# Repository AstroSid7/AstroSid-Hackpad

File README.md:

# AstroSid-Hackpad
A custom 6-key mechanical macropad featuring a rotary encoder for media and volume control. Designed with a 2-layer PCB, a 3D-printed case, and powered by the Seeed XIAO RP2040 using KMK (CircuitPython) firmware.

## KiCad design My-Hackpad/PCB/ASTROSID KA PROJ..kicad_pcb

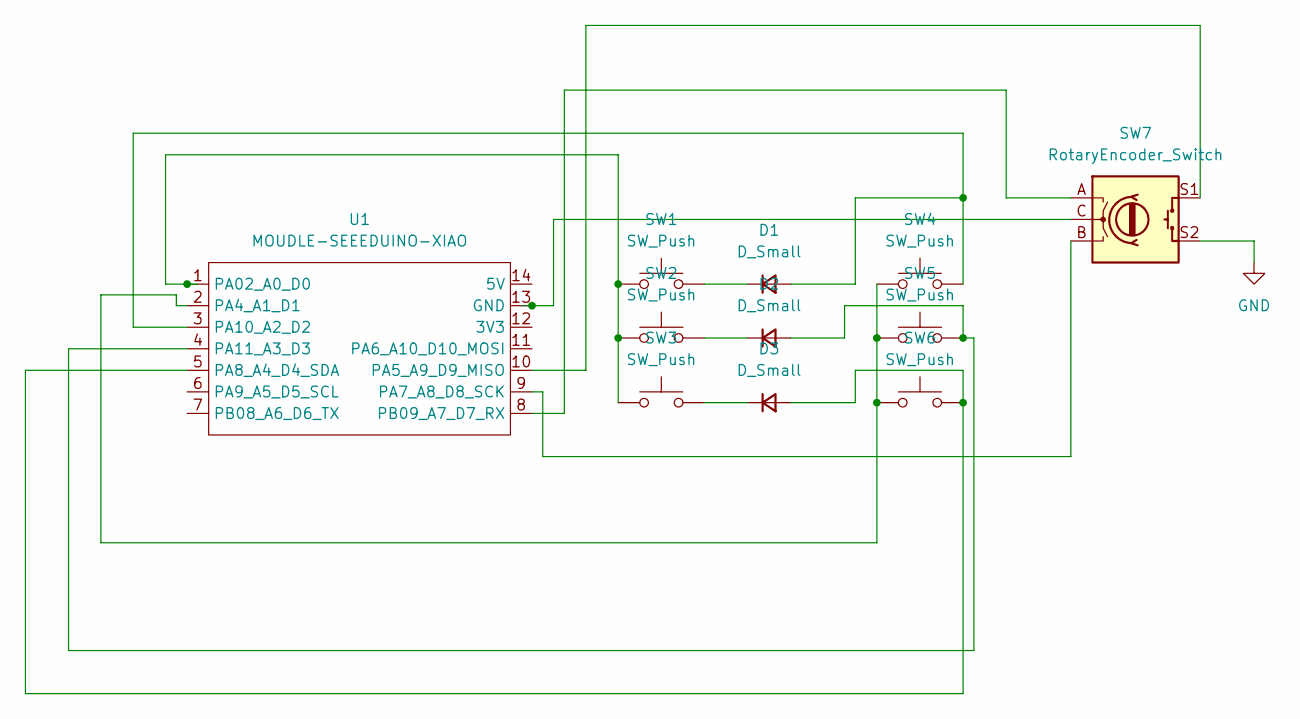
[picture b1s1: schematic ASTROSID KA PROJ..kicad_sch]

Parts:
D1, D2, D3: D_Small; D_SOD-123
SW1, SW2, SW3, SW4, SW5, SW6: SW_Push; SW_Cherry_MX_1.00u_PCB
SW7: RotaryEncoder_Switch; RotaryEncoder_Alps_EC11E-Switch_Vertical_H20mm
U1: MOUDLE-SEEEDUINO-XIAO; XIAO-Generic-Hybrid-14P-2.54-21X17.8MM

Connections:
GND: SW7.S2
unnamed: D1.2 (A), SW4.2, U1.3 (PA10_A2_D2)
unnamed: D1.1 (K), SW1.2
unnamed: D2.2 (A), SW5.2, U1.4 (PA11_A3_D3)
unnamed: D2.1 (K), SW2.2
unnamed: D3.2 (A), SW6.2, U1.5 (PA8_A4_D4_SDA)
unnamed: D3.1 (K), SW3.2
unnamed: SW7.C, U1.13 (GND)
unnamed: SW1.1, SW2.1, SW3.1, U1.1 (PA02_A0_D0)
unnamed: SW4.1, SW5.1, SW6.1, U1.2 (PA4_A1_D1)
unnamed: SW7.S1, U1.10 (PA5_A9_D9_MISO)
unnamed: SW7.B, U1.9 (PA7_A8_D8_SCK)
unnamed: SW7.A, U1.8 (PB09_A7_D7_RX)

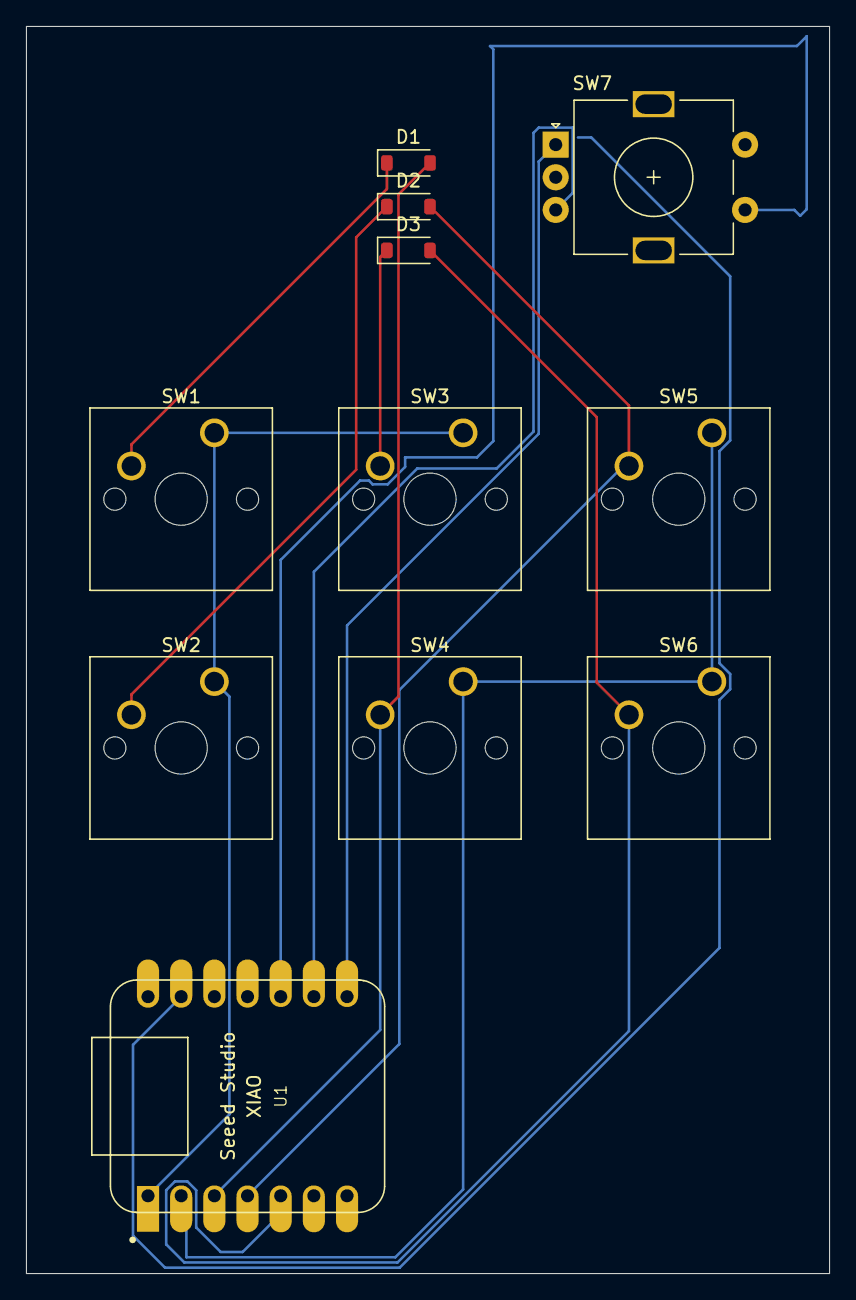
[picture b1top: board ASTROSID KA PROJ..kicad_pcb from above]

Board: 2 copper layers, 61.5 x 95.5 mm, 11 parts (0 on the bottom side), 12 nets.
